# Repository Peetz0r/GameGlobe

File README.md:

# GameGlobe
GameGlobe cheap handheld game console, Arduino based

# Bill Of Materials
Part			|  Price	|  Amount	|  Cost p.p.	|  Link
------------------------|--------------:|--------------:|--------------:|------------------------------
PCB			|  $28,00	|    20		|  $1,40	|  http://dirtypcbs.com/
Arduino Nano		|  $ 1,87	|     1		|  $1,87	|  http://www.aliexpress.com/item//32242060255.html
3310 display		|  $ 3,07	|     2		|  $1,54	|  http://www.aliexpress.com/item//32438248013.html
9V clip			|  $ 1,25	|    20		|  $0,06	|  http://www.aliexpress.com/item//32353434826.html
D-Pad (SKQUCAA010)	|  $10,93	|    20		|  $0,55	|  http://www.aliexpress.com/item//32354178656.html
Power switch		|  $ 3,50	|   100		|  $0,04	|  http://www.aliexpress.com/item//32390211893.html
Speaker			|  $ 6,18	|    50		|  $0,13	|  http://www.aliexpress.com/item//32438430293.html
Resistors		|    free	|  many		|   free	|  

Total $5,43

Note: somehow 20 boards is cheaper per piece than 30. So we'll buy 40 (2*20).
And the displays have some shipping costs (but they are the cheapest regardless).

Note: check all of the parts for hidden shippig costs when you order larger numbers.
It may be that a seller changes this without me knowing. Especially some of the Arduino sellers.

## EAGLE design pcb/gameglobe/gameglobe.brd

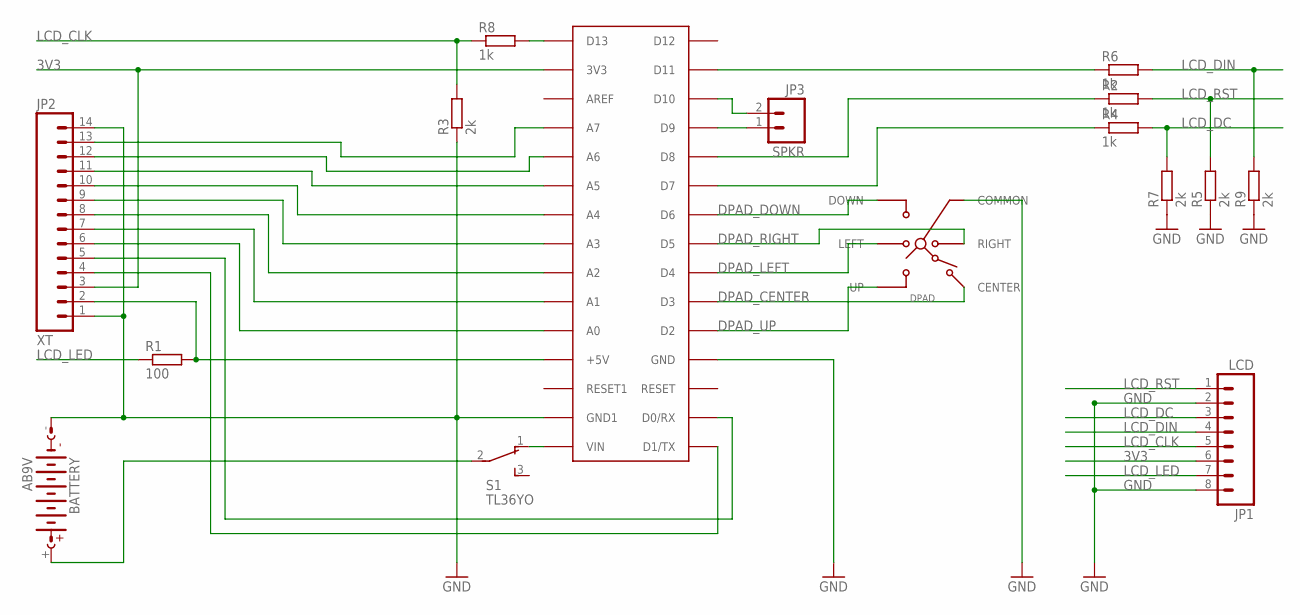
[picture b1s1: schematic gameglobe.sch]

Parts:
ARDUINO_NANO: ARDUINONANO; PDIP-32
BATTERY: AB9V
DPAD: SKQUCAA010; SKQU
JP1: LCD; 1X08_ROUND
JP2: XT; 1X14-LONGPADS
JP3: SPKR; 1X02
R1: 100; 0411/15
R2, R4, R6, R8: 1k; 0411/15
R3, R5, R7, R9: 2k; 0411/15
S1: TL36YO; TL3XYO

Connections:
3V3: ARDUINO_NANO.3V3, JP1.6, JP2.3
5V: ARDUINO_NANO.+5V, JP2.2, R1.2
A0: ARDUINO_NANO.A0, JP2.6
A1: ARDUINO_NANO.A1, JP2.7
A2: ARDUINO_NANO.A2, JP2.8
A3: ARDUINO_NANO.A3, JP2.9
A4: ARDUINO_NANO.A4, JP2.10
A5: ARDUINO_NANO.A5, JP2.11
A6: ARDUINO_NANO.A6, JP2.12
A7: ARDUINO_NANO.A7, JP2.13
DPAD_CENTER: ARDUINO_NANO.D3, DPAD.CENTER
DPAD_DOWN: ARDUINO_NANO.D6, DPAD.DOWN
DPAD_LEFT: ARDUINO_NANO.D4, DPAD.LEFT
DPAD_RIGHT: ARDUINO_NANO.D5, DPAD.RIGHT
DPAD_UP: ARDUINO_NANO.D2, DPAD.UP
GND: ARDUINO_NANO.GND, ARDUINO_NANO.GND1, BATTERY.-, DPAD.COMMON, JP1.2, JP1.8, JP2.1, JP2.14, R3.1, R5.1, R7.1, R9.1
LCD_CLK: JP1.5, R3.2, R8.1
LCD_DC: JP1.3, R4.2, R7.2
LCD_DIN: JP1.4, R6.2, R9.2
LCD_LED: JP1.7, R1.1
LCD_RST: JP1.1, R2.2, R5.2
unnamed: ARDUINO_NANO.D13, R8.2
unnamed: ARDUINO_NANO.D11, R6.1
unnamed: ARDUINO_NANO.D8, R2.1
unnamed: ARDUINO_NANO.D9, JP3.1
unnamed: ARDUINO_NANO.VIN, S1.1 (O)
unnamed: BATTERY.+, S1.2
unnamed: ARDUINO_NANO.D10, JP3.2
unnamed: ARDUINO_NANO.D7, R4.1
RX: ARDUINO_NANO.D0/RX, JP2.5
TX: ARDUINO_NANO.D1/TX, JP2.4

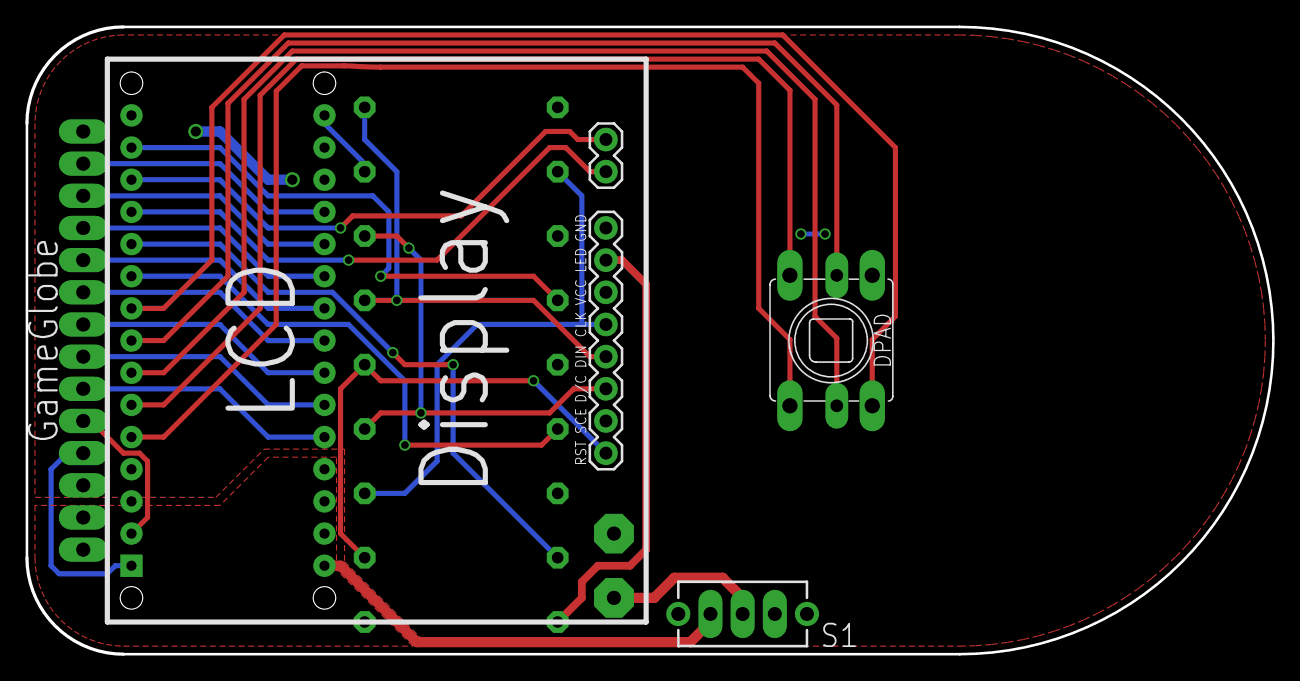
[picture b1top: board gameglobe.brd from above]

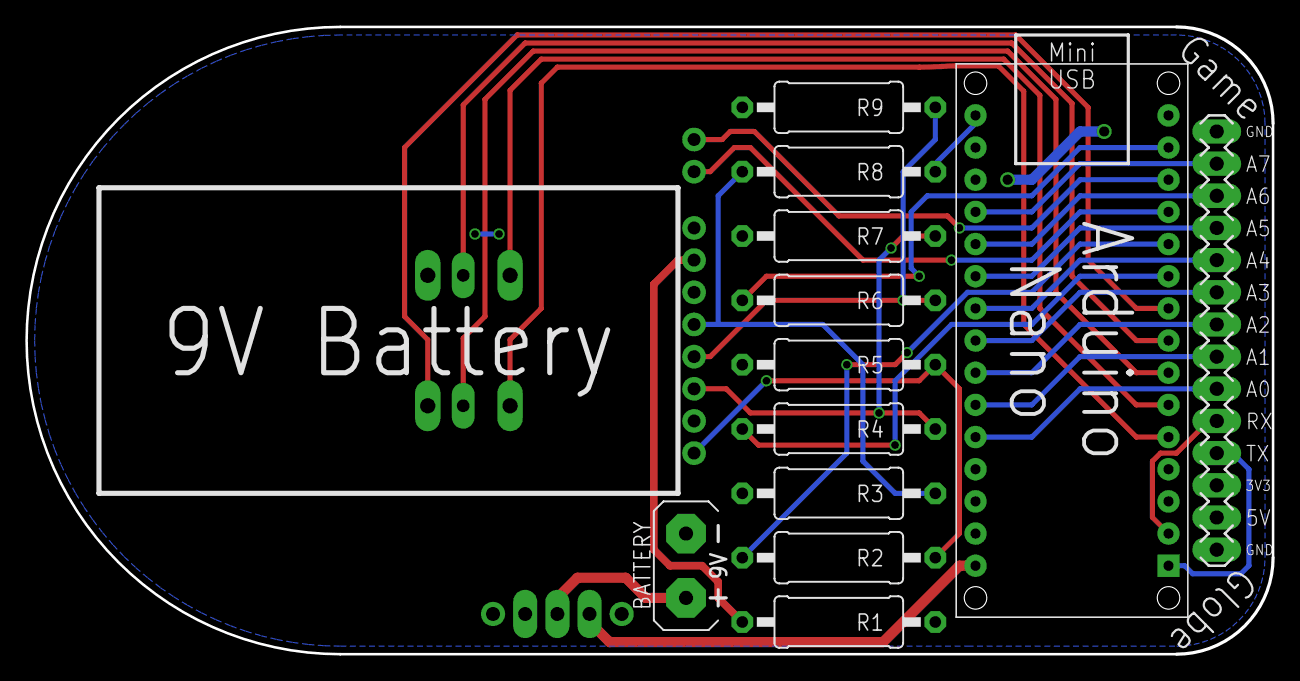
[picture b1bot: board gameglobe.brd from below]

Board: 2 copper layers, 98.4 x 49.5 mm, 16 parts (12 on the bottom side), 31 nets.

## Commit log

2015-08-23 Parts list
2015-08-23 Added logo
2015-08-23 Fix counting mistake
2015-08-23 add initial schematic an board very early version
2015-08-24 BOM is sortof complete, and PCB is more complete-ish now
2015-08-25 Added dpad part number
2015-08-28 Add backlight wire and resistor
2015-08-28 Add custom DRC
2015-08-28 Add early mockup. Physical paper version available as well ;)
2015-08-28 Create inotools setup Add Adafruit libraries Create basic sketch (which doesn't do anything really)
2015-08-28 Reduce filesize of huge hires gimp file
2015-08-28 Improve net names and board layout
2015-08-28 Update BOM with less parts and cheaper and better PCBs
2015-08-28 oops
2015-08-29 Updated DRU file; Improved PCB layout; Added rounded edges and mount holes
2015-08-30 More PCB improvements, moved the Nano a bit sideways and improved battery mounting holes
2015-08-30 Many PCB improvements. Actually the first version where everything (joystick, lcd, nano) is centered on the board
2015-08-30 Fix and add own arduino Improve silkscreen texts
2015-08-30 Added LCD Display outline
2015-08-30 Neated-up scheme
2015-08-30 Update gitignore for inotool build files
2015-08-30 Improved silkscreen
2015-08-30 Remove all libraries
2015-08-30 re-add libraries as git submodules
2015-08-30 Add somewhat useful sketch using all of those libraries
2015-08-30 Reverse button logic
2015-09-01 Added splash screen and some basic structure to sketch
2015-09-01 Added power switch to pcb. LCD pin labels on slikscreen
2015-09-01 Update list of parts to include power switch
2015-09-01 Add splash screen source file
2015-09-02 Set LED resistor value to 100 (after testing with prototype); Move some silkscreen items around; Enable all needed layers in Eagle
2015-09-02 Add dirtypcbs CAM job
2015-09-02 Somehow 2x20 is cheaper (per piece) than 1x30
2015-09-04 Almost complete snake implementation with some memory issues
2015-09-06 Fixed snake issues; Finished snake; Implemented basic highscore system;
2015-09-06 Made awesome silkscreen art
2015-09-06 Remove outdated pdf file
2015-09-06 Speaker is back!
2015-09-06 Changed to cheaper speaker (flat piezo buzzer); Mount speaker belof display, add connector for speaker; Improve 9V connector; Improve silkscreen again;
2015-09-06 Update mockup image
2015-09-07 Reduced silkscreen text size
2015-09-07 Change display supplier (and color); somehow the new pinout is identical to the old one :)
2015-09-07 Oops, forgot to render png (and direct links to png's on github are nice to have)
2015-09-08 Add QR code; Reduce top corner radiuses; Fix/improve some routing things;
2015-09-09 Update readme with better aliexpress links
2015-09-23 Basic Tone library usage
2015-09-23 change wiring to use different pins for the speaker with ToneAC library (and also all the buttons)
2015-09-23 Add toneAC library
2015-09-23 Use toneAC, also change pin numbers everywhere
2015-09-23 change pin numbers (just as in the code, see previous commit), also use ground plane
2015-09-24 Add power planes for 3V3 and 5V to add a more premium feeling to the board design (whatever this may mean)
2015-09-24 Improved power plane layout, also improved silkscreen, updated mockup image with new pcb renders
2015-09-24 Increased pad sizes, swapped DPAD left/right pins for better routing, improved silkscreen text
2015-09-25 Got my arduino elsewhere (because they suddenly added shipping)
2015-09-25 Rotate part in schematic for neater layout, pcb unchanged
2015-09-25 Add volume with memory and menu display, fix reset pin, change eeprom addresses
2015-09-26 Resistor renaming and related silkscreen fixes
2015-09-26 Updated gimp file and png file since previous commit
2015-09-26 Changed Arduino seller again, because of shipping costs
2015-09-30 Make multiple button presses not stack ytogether in one frame. The old behaviour was that, when moving left, and pressing 'up' and 'right' quickly after eachother, would kill the snake. now it doesn'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
2015-10-14 Slightly improve code neatness, also some beginnings of flappy something
2015-10-15 Renamed Flappy Bird to FlappySmile and actually wrote the thing. It's ugly!
2015-10-15 updated gitignore
2015-11-25 Added image version of eagle files
2016-01-28 New generic silkscreen design
2016-02-16 ano support (ano is a fork of inotool, compatible with newer arduino ide versions)
2016-03-29 Replaced qr code splash screen (which was unscannable) with a personalised splash screen stating the name of the owner
    You can flash this with "./nameflash.sh YourName"
    Names up to 14 characters are supported
2016-03-29 I think flappysmile is okay now
2016-03-29 make the snake eating sound less crap
2016-03-29 created game over sfx
2016-03-29 Tetris beginnings. drawing seems okay for now
2016-03-29 volume bar now displays a cross when set to 0/mute
2016-04-08 Basics of tetris working. no scoring, and very broken colission detection
2016-04-08 colission detection looks okay now. yay :)
2016-04-09 rotating seems to work okay now
2016-04-09 added line clearing and scoring moved drawing to the side to allow for next shape and score
2016-05-05 Changed PCB supplier (pcb color) from blue to read, removed QR code from mockup image
2016-05-05 Properly initiali(s/z)e tetris 'field' to all zero Make volume an uint instead of int Sligtly finetune difficulty
2016-05-05 Only actyallu upload if build went okay (and only build if clean went okay)
2016-05-05 binary game logic bug fixed
    the bug caused the game to remove not only the correct line but all lines below it as well
2016-05-05 believe it or not, this saves 1084 bytes of arduino space
2016-05-05 Remove this and save another handful of bytes. 22 or so. dunno. #everybytematters #hashtagsongithub #hipsterfornoreason
2016-05-13 More beep! (on tetris row removed)
2017-07-18 fixed broken reference
2017-07-18 make it arduino-ide-compatible again. I probably broke ano/ino compatibility right now
2017-07-18 properly end ano/ino compatibility

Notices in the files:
parts and their libraries:
SparkFun-Connectors: Licensing: Creative Commons ShareAlike 4.0 International - https://creativecommons.org/licenses/by-sa/4.0
